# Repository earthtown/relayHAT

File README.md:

# relayHAT
4 channel relay HAT for the Raspberry Pi

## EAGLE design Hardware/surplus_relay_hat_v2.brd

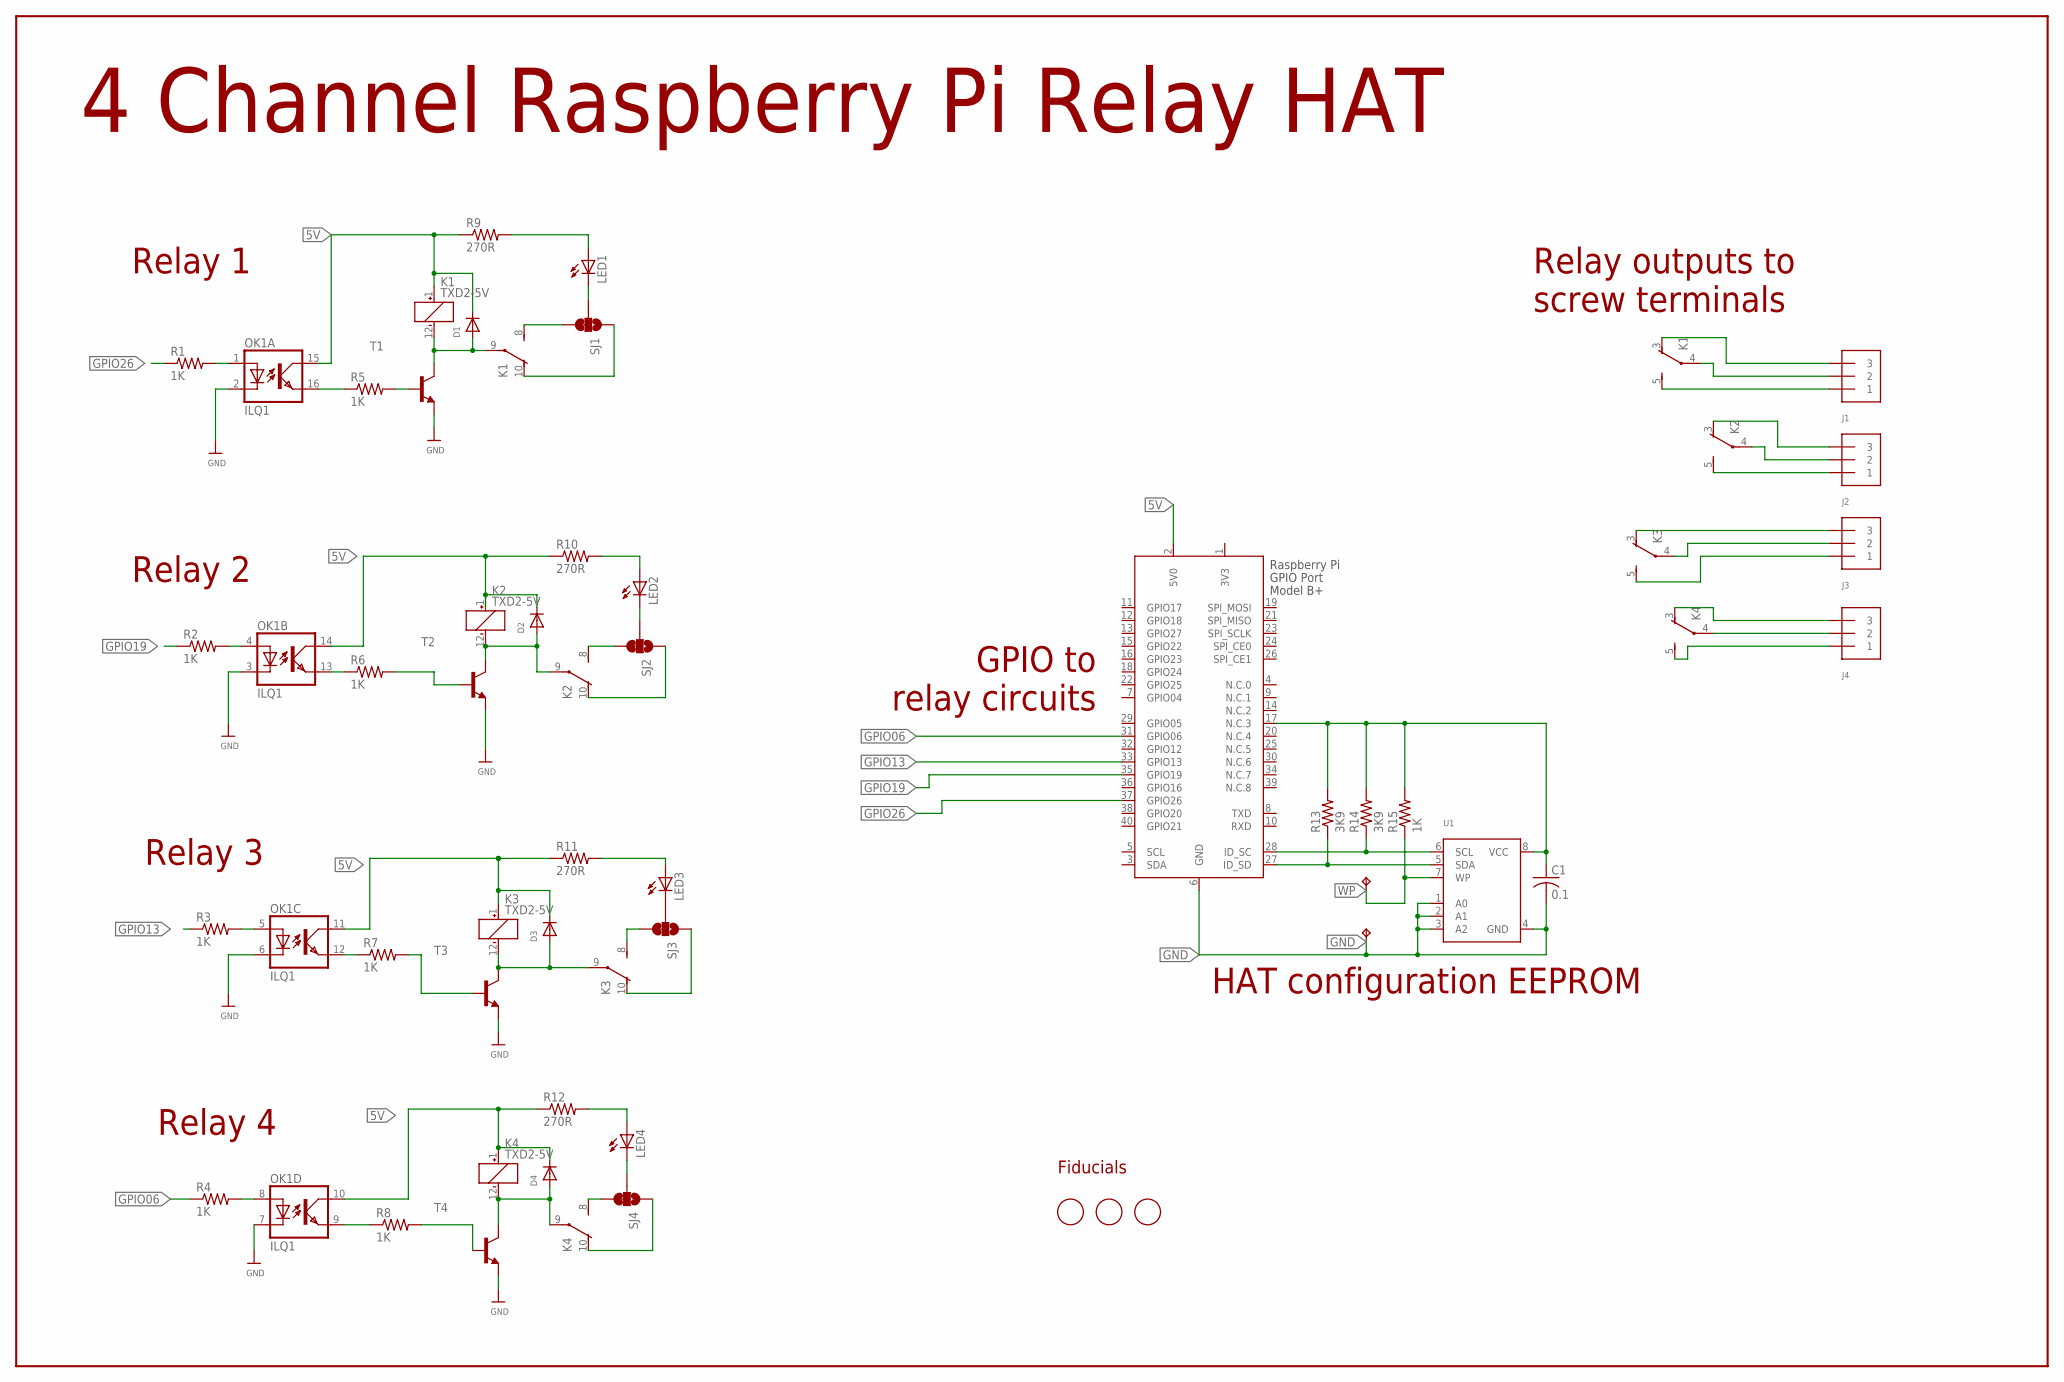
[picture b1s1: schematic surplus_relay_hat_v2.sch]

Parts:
C1: 0.1; C0805K
CFG: TPTP11R; TP11R
D1, D2, D3, D4: DIODE_SOD-123FL; SOD-123FL
GND: TPTP11R; TP11R
J1, J2, J3, J4: TERMBLOCK_1X3; TERMBLOCK_1X3-3.5MM
K1, K2, K3, K4: TXD2-5V; TXD2
LED1, LED2, LED3, LED4: LEDCHIP-LED0805; CHIP-LED0805
OK1: ILQ1; DIL16
R1, R2, R3, R4, R5, R6, R7, R8, R15: 1K; R0603
R9, R10, R11, R12: 270R; R0603
R13, R14: 3K9; R0603
SJ1, SJ2, SJ3, SJ4: JUMPER-PAD-3-2OF3_NC_BY_TRACE; PAD-JUMPER-3-2OF3_NC_BY_TRACE_YES_SILK_FULL_BOX
T1, T2, T3, T4: MMBT2222ALT1-NPN-SOT23-BEC; SOT23-BEC
U1: EEPROM_I2C_SOIC8_GENERIC; SOIC8_150MIL
U$2, U$12, U$13: FIDUCIAL; FIDUCIAL_1MM
X1: RASPI_BOARD_B+_H; RASPI_BOARD_B+HAT

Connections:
3V3: X1.1 (3V3)
5V: D1.C, D2.C, D3.C, D4.C, K1.1 (+), K2.1 (+), K3.1 (+), K4.1 (+), OK1.10 (COL), OK1.11 (COL), OK1.14 (COL), OK1.15 (COL), R9.1, R10.1, R11.1, R12.1, X1.2 (5V0)
GND: C1.2, GND.TP, OK1.2 (C), OK1.3 (C), OK1.6 (C), OK1.7 (C), T1.E, T2.E, T3.E, T4.E, U1.1 (A0), U1.2 (A1), U1.3 (A2), U1.4 (GND), X1.6 (GND)
GPIO06: R4.1, X1.31 (GPIO06)
GPIO13: R3.1, X1.33 (GPIO13)
GPIO19: R2.1, X1.35 (GPIO19)
GPIO26: R1.1, X1.37 (GPIO26)
ID-SCL: R14.1, U1.6 (SCL), X1.28 (ID_SC)
ID-SDA: R13.1, U1.5 (SDA), X1.27 (ID_SD)
unnamed: R5.2, T1.B
unnamed: OK1.16 (EMIT), R5.1
unnamed: OK1.1 (A), R1.2
unnamed: D1.A, K1.9, K1.12 (-), T1.C
unnamed: J1.2, K1.4
unnamed: J1.1, K1.5 (S)
unnamed: J1.3, K1.3 (O)
unnamed: J2.1, K2.5 (S)
unnamed: OK1.4 (A), R2.2
unnamed: D2.A, K2.9, K2.12 (-), T2.C
unnamed: R6.2, T2.B
unnamed: J2.2, K2.4
unnamed: OK1.12 (EMIT), R7.1
unnamed: J2.3, K2.3 (O)
unnamed: OK1.5 (A), R3.2
unnamed: OK1.8 (A), R4.2
unnamed: D4.A, K4.9, K4.12 (-), T4.C
unnamed: R7.2, T3.B
unnamed: OK1.9 (EMIT), R8.1
unnamed: LED1.C, SJ1.2
unnamed: J3.2, K3.4
unnamed: J3.1, K3.5 (S)
unnamed: J3.3, K3.3 (O)
unnamed: R8.2, T4.B
unnamed: K1.8 (S), SJ1.3
unnamed: J4.1, K4.5 (S)
unnamed: J4.2, K4.4
unnamed: J4.3, K4.3 (O)
unnamed: LED1.A, R9.2
unnamed: K1.10 (O), SJ1.1
unnamed: K4.10 (O), SJ4.1
unnamed: LED4.A, R12.2
unnamed: LED3.A, R11.2
unnamed: K4.8 (S), SJ4.3
unnamed: LED4.C, SJ4.2
unnamed: LED2.A, R10.2
unnamed: C1.1, R13.2, R14.2, R15.2, U1.8 (VCC), X1.17 (N.C.3)
unnamed: OK1.13 (EMIT), R6.1
unnamed: D3.A, K3.9, K3.12 (-), T3.C
unnamed: K3.8 (S), SJ3.3
unnamed: K3.10 (O), SJ3.1
unnamed: LED3.C, SJ3.2
unnamed: LED2.C, SJ2.2
unnamed: K2.8 (S), SJ2.3
unnamed: K2.10 (O), SJ2.1
N.C.1: X1.9 (N.C.1)
WP: CFG.TP, R15.1, U1.7 (WP)

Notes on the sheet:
Fiducials
4 Channel Raspberry Pi Relay HAT
Relay 1
Relay 2
Relay 3
Relay 4
HAT configuration EEPROM
GPIO to relay circuits
Relay outputs to screw terminals

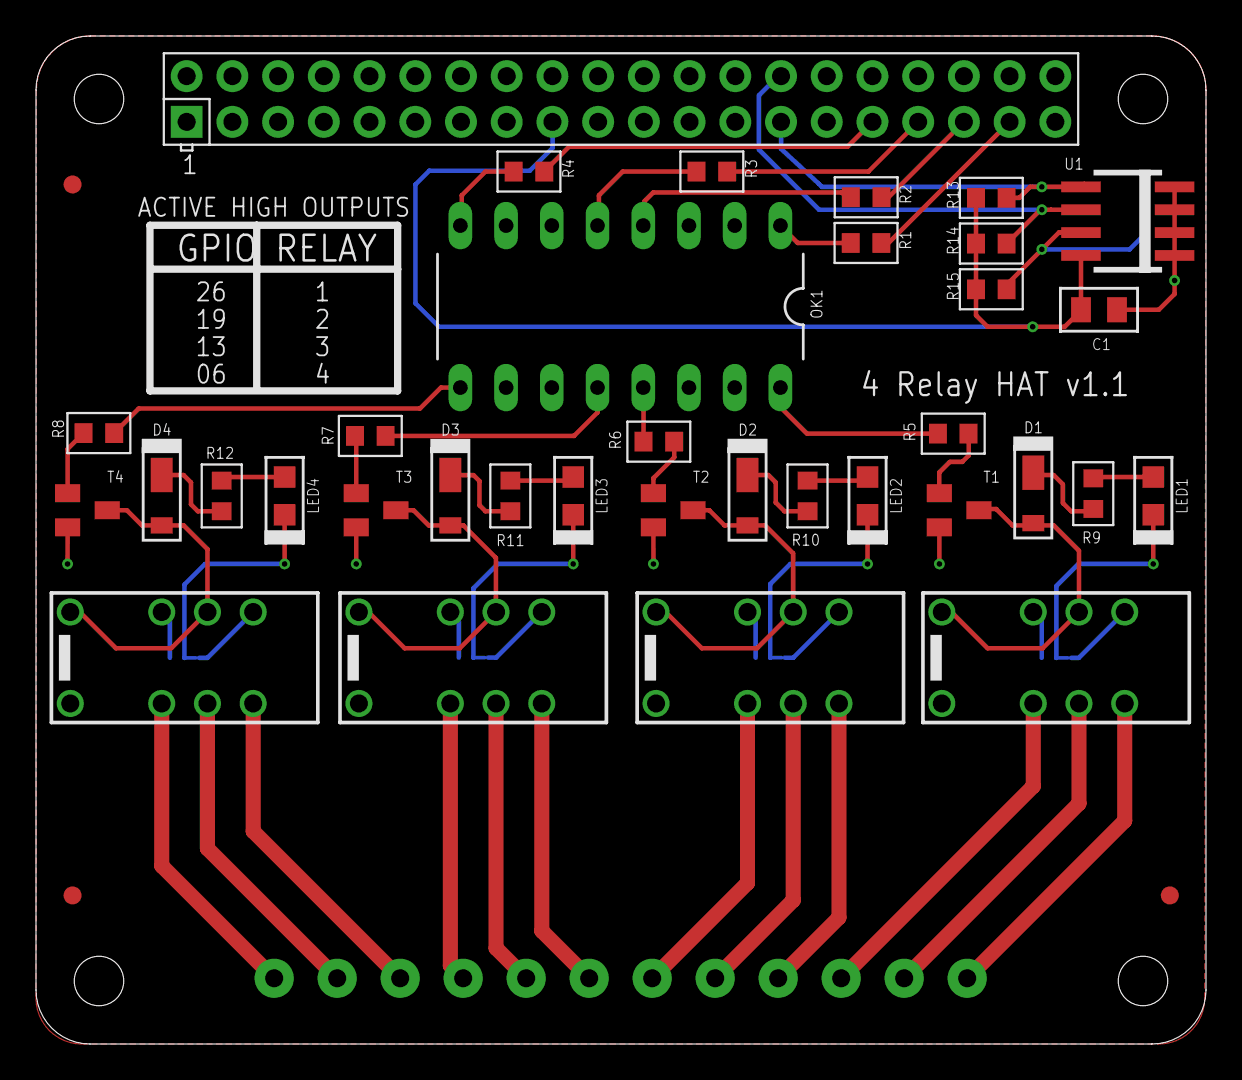
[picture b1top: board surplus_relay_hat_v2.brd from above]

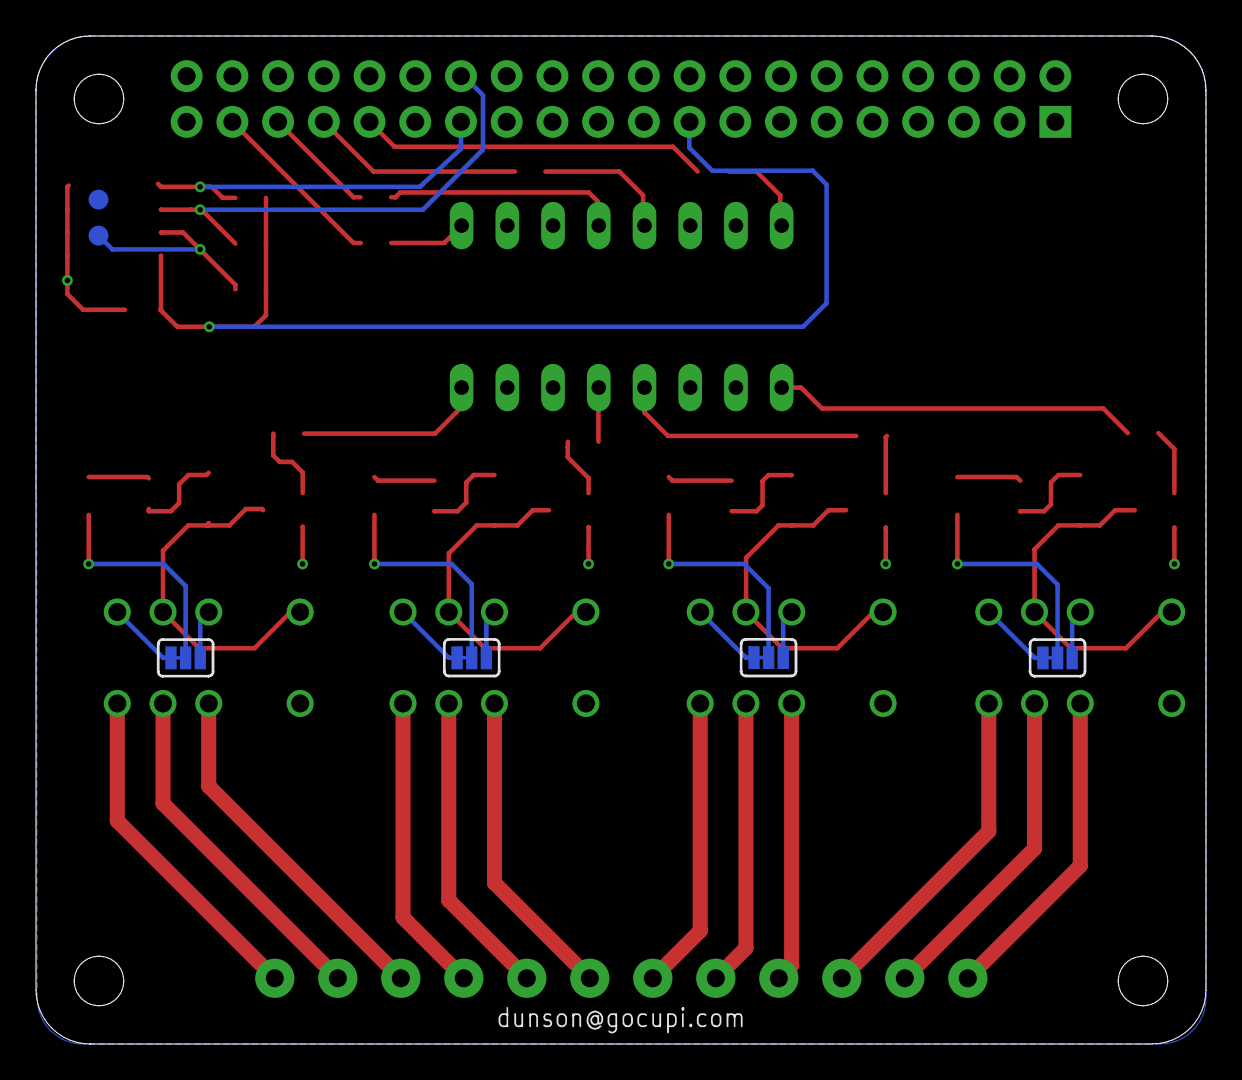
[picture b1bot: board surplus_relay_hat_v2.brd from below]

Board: 2 copper layers, 65.0 x 56.0 mm, 48 parts (6 on the bottom side), 54 nets.

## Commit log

2017-03-12 Added hardware files
    Eagle files and PDFs
2017-03-19 Missing license and attribution info.
2017-03-19 Added license and attribution.

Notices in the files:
parts and their libraries:
TL2575: This work is placed in the public domain, and may be freely used for commercial and non-commercial work with the following conditions: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
SparkFun-Passives: Licensing: Creative Commons ShareAlike 4.0 International - https://creativecommons.org/licenses/by-sa/4.0
